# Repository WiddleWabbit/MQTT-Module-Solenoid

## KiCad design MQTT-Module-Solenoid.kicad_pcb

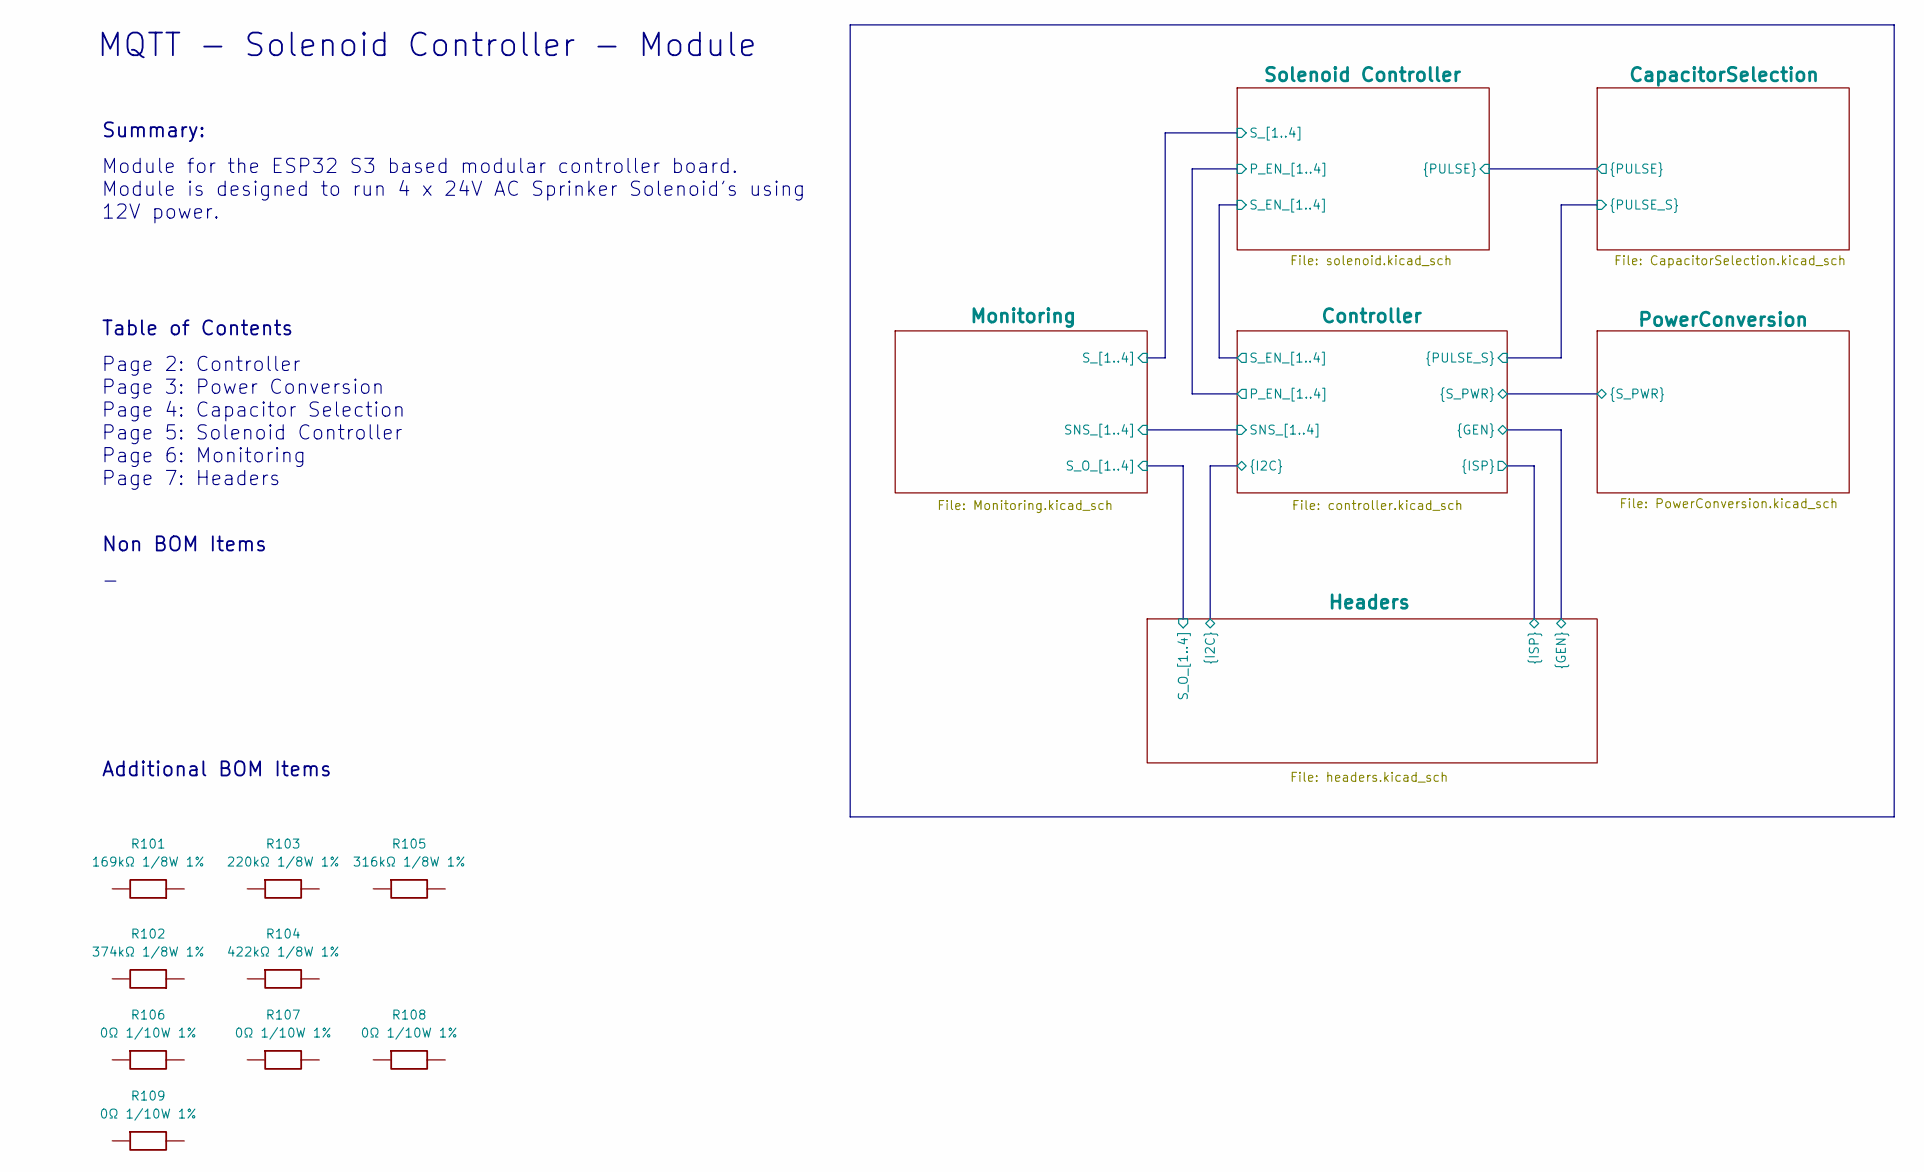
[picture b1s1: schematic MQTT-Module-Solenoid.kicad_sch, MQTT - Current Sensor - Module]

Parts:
R101: 169kΩ 1/8W 1%; RESC2013X65N; Manufacturer Part No 0805W8F1693T5E; JLCPCB Part # C17488
R102: 374kΩ 1/8W 1%; RESC2013X65N; Manufacturer Part No CRCW0805374KFKEA; JLCPCB Part # C2080711
R103: 220kΩ 1/8W 1%; RESC2013X65N; Manufacturer Part No 0805W8F2203T5E; JLCPCB Part # C17556
R104: 422kΩ 1/8W 1%; RESC2013X65N; Manufacturer Part No 0805W8F4223T5E; JLCPCB Part # C17688
R105: 316kΩ 1/8W 1%; RESC2013X65N; Manufacturer Part No 0805W8F3163T5E; JLCPCB Part # C407398
R106, R107, R108, R109: 0Ω 1/10W 1%; RESC1608X55N; Manufacturer Part No 0603WAF0000T5E; JLCPCB Part # C21189

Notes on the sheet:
MQTT - Solenoid Controller - Module
Additional BOM Items
Summary:
Non BOM Items
Page 2: Controller Page 3: Power Conversion Page 4: Capacitor Selection Page 5: Solenoid Controller Page 6: Monitoring Page 7: Headers
Table of Contents
Module for the ESP32 S3 based modular controller board. Module is designed to run 4 x 24V AC Sprinker Solenoid's using 12V power.

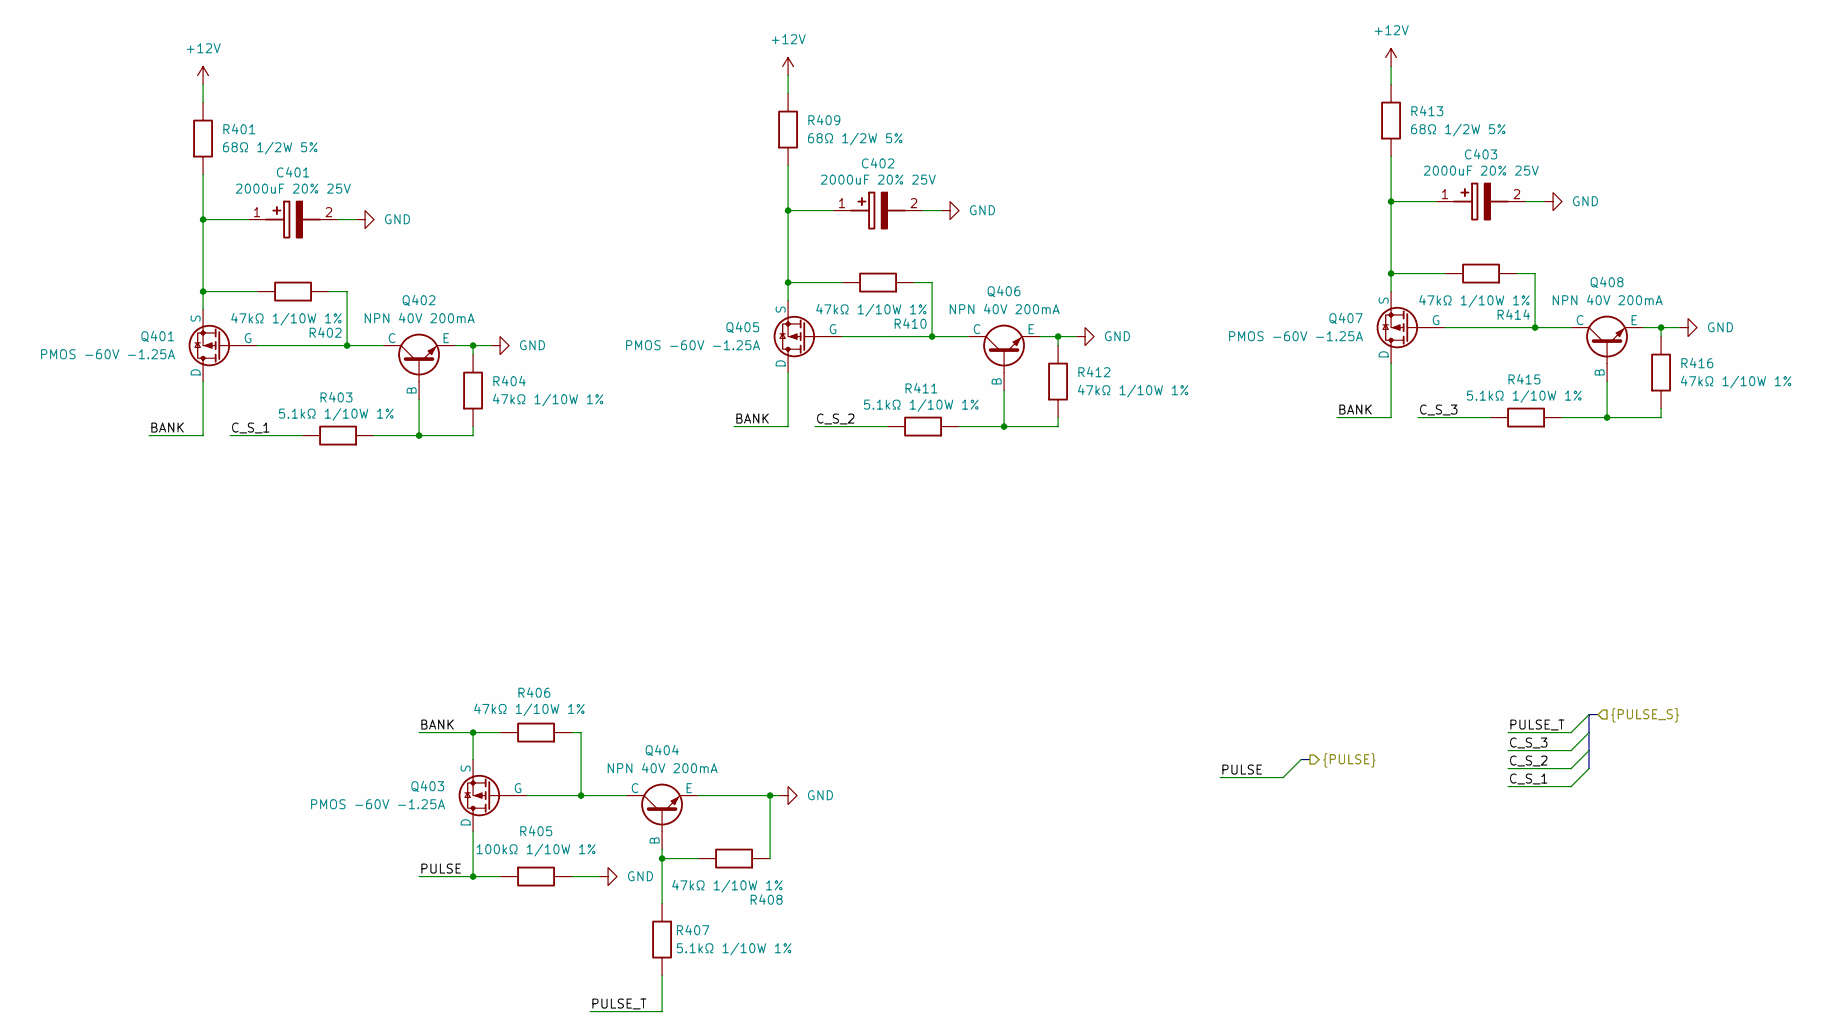
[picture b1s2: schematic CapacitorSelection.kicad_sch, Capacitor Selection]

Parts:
C401, C402, C403: 2000uF 20% 25V; CP_Radial_D12.5mm_P5.00mm; Mouser Part Number 667-EEU-FP1E202
Q401, Q403, Q405, Q407: PMOS -60V -1.25A; SOT-23-3 - FDN5618P; Manufacturer Part No FDN5618P; JLCPCB Part # C400792
Q402, Q404, Q406, Q408: NPN 40V 200mA; SOT-23; Manufacturer Part No MMBT3904LT1G; JLCPCB Part # C81464
R401, R409, R413: 68Ω 1/2W 5%; R_1210_3225Metric; Manufacturer Part No 1210W2J0680T5E; JLCPCB Part # C473019
R402, R404, R406, R408, R410, R412, R414, R416: 47kΩ 1/10W 1%; RESC1608X55N; Manufacturer Part No 0603WAF4702T5E; JLCPCB Part # C25819
R403, R407, R411, R415: 5.1kΩ 1/10W 1%; RESC1608X55N; Mouser Part Number 303-0603WAF5101T5E
R405: 100kΩ 1/10W 1%; RESC1608X55N; Mouser Part Number 303-0805W8F1003T5E

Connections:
+12V: R401.2, R409.2, R413.2; also elsewhere on the board
/CapacitorSelection/BANK: Q401.3 (D), Q403.2 (S), Q405.3 (D), Q407.3 (D), R406.2
/CapacitorSelection/C_S_1: R403.2; also elsewhere on the board
/CapacitorSelection/C_S_2: R411.2; also elsewhere on the board
/CapacitorSelection/C_S_3: R415.2; also elsewhere on the board
/CapacitorSelection/PULSE: Q403.3 (D), R405.1; also elsewhere on the board
/CapacitorSelection/PULSE_T: R407.2; also elsewhere on the board
GND: C401.2 (-), C402.2 (-), C403.2 (-), Q402.2 (E), Q404.2 (E), Q406.2 (E), Q408.2 (E), R404.2, R405.2, R408.1, R412.2, R416.2; also elsewhere on the board
unnamed: C401.1 (+), Q401.2 (S), R401.1, R402.2
unnamed: C402.1 (+), Q405.2 (S), R409.1, R410.2
unnamed: C403.1 (+), Q407.2 (S), R413.1, R414.2
unnamed: Q401.1 (G), Q402.3 (C), R402.1
unnamed: Q402.1 (B), R403.1, R404.1
unnamed: Q403.1 (G), Q404.3 (C), R406.1
unnamed: Q404.1 (B), R407.1, R408.2
unnamed: Q405.1 (G), Q406.3 (C), R410.1
unnamed: Q406.1 (B), R411.1, R412.1
unnamed: Q407.1 (G), Q408.3 (C), R414.1
unnamed: Q408.1 (B), R415.1, R416.1

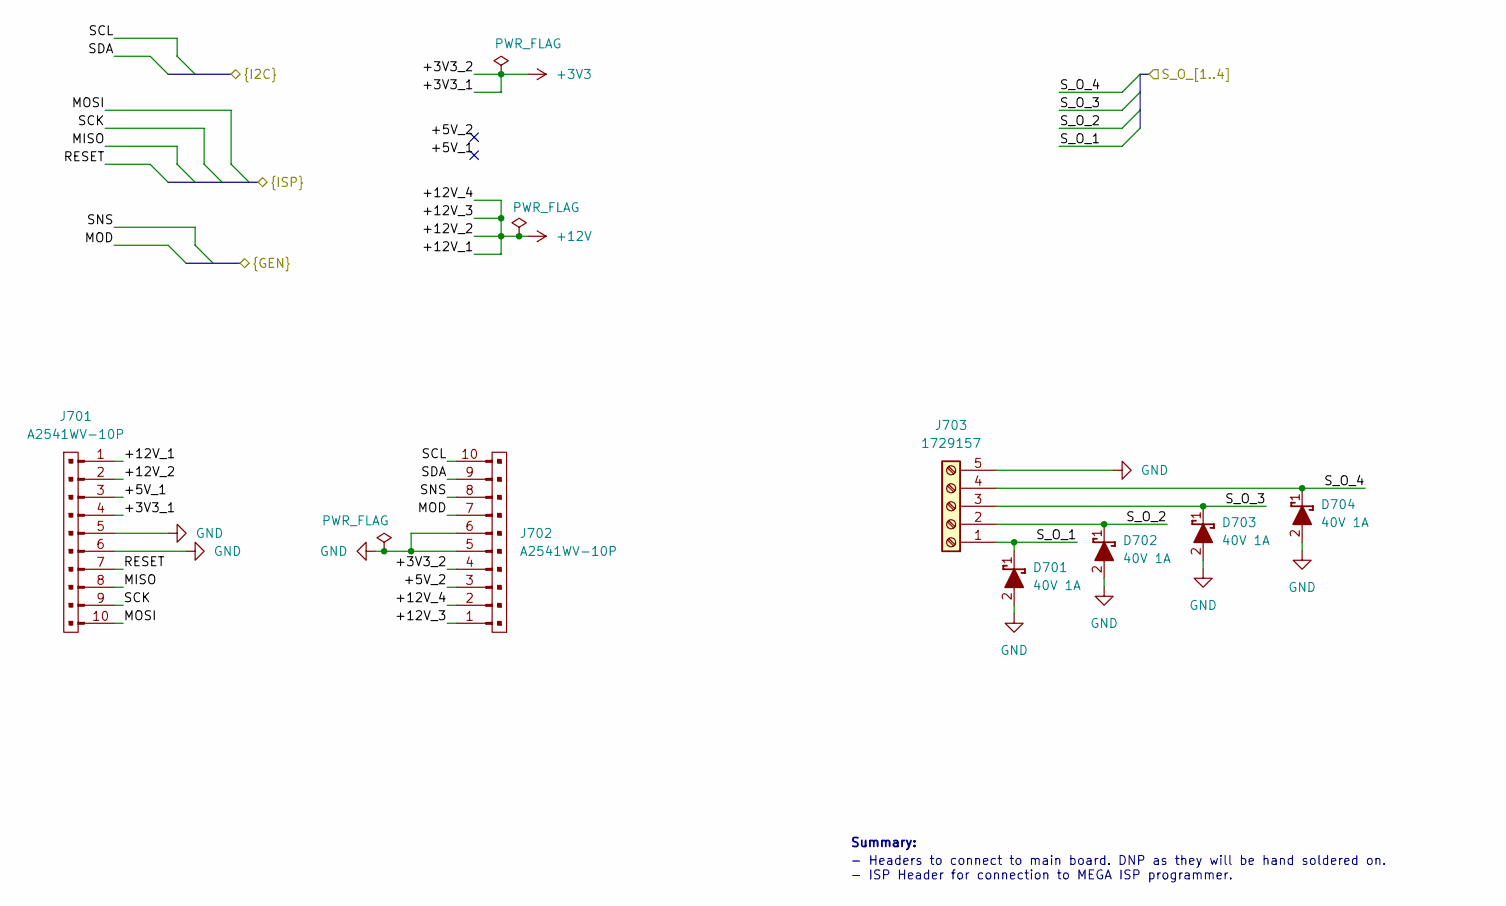
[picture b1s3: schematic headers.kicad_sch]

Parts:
D701, D702, D703, D704: 40V 1A; D_SOD-323F; Manufacturer Part No 1N5819WS; JLCPCB Part # C191023
J701, J702: A2541WV-10P; PinHeader_1x10_P2.54mm_Vertical_Male; Manufacturer Part No A2541WV-10P; JLCPCB Part # C225485
J703: 1729157; Mouser Part Number 651-1729157

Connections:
+3V3: J701.4, J702.4; also elsewhere on the board
+12V: J701.1, J701.2, J702.1, J702.2; also elsewhere on the board
/Controller/MISO: J701.8; also elsewhere on the board
/Controller/MOD: J702.7; also elsewhere on the board
/Controller/MOSI: J701.10; also elsewhere on the board
/Controller/RESET: J701.7; also elsewhere on the board
/Controller/SCK: J701.9; also elsewhere on the board
/Controller/SCL: J702.10; also elsewhere on the board
/Controller/SDA: J702.9; also elsewhere on the board
/Controller/SNS: J702.8; also elsewhere on the board
/Headers/+5V_1: J701.3
/Headers/+5V_2: J702.3
/Headers/S_O_1: D701.1 (K), J703.1; also elsewhere on the board
/Headers/S_O_2: D702.1 (K), J703.2; also elsewhere on the board
/Headers/S_O_3: D703.1 (K), J703.3; also elsewhere on the board
/Headers/S_O_4: D704.1 (K), J703.4; also elsewhere on the board
GND: D701.2 (A), D702.2 (A), D703.2 (A), D704.2 (A), J701.5, J701.6, J702.5, J702.6, J703.5; also elsewhere on the board

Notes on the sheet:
Summary:
- Headers to connect to main board. DNP as they will be hand soldered on. - ISP Header for connection to MEGA ISP programmer.

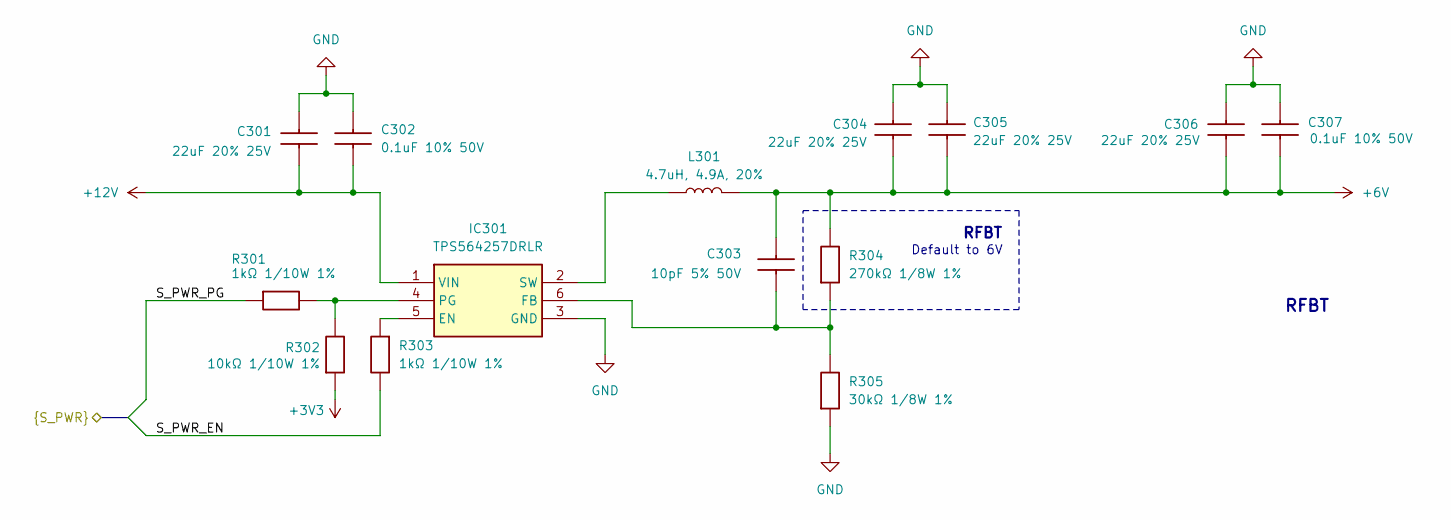
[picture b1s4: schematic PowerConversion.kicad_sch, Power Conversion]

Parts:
C301, C304, C305, C306: 22uF 20% 25V; CAPC2012X75N; Manufacturer Part No CL21A226MAQNNNE; JLCPCB Part # C45783
C302, C307: 0.1uF 10% 50V; CAPC1608X90N; Mouser Part Number 603-CC603KRX7R9BB104
C303: 10pF 5% 50V; CAPC1608X90N; Manufacturer Part No CL10C100JB8NNNC; JLCPCB Part # C1634
IC301: TPS564257DRLR; SOT-563; Mouser Part Number 595-TPS564257DRLR
L301: 4.7uH, 4.9A, 20%; SMD,6x6mm; Manufacturer Part No SMNR6045-4R7MT; JLCPCB Part # C135302
R301, R303: 1kΩ 1/10W 1%; RESC1608X55N; Manufacturer Part No 0603WAF1001T5E; JLCPCB Part # C21190
R302: 10kΩ 1/10W 1%; RESC1608X55N; Mouser Part Number 303-0805W8F1002T5E
R304: 270kΩ 1/8W 1%; RESC2013X65N; Manufacturer Part No 0805W8F2703T5E; JLCPCB Part # C17589
R305: 30kΩ 1/8W 1%; RESC2013X65N; Manufacturer Part No 0805W8F3002T5E; JLCPCB Part # C17621

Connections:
+3V3: R302.1; also elsewhere on the board
+6V: C303.2, C304.1, C305.1, C306.1, C307.1, L301.2, R304.2; also elsewhere on the board
+12V: C301.1, C302.1, IC301.1 (VIN); also elsewhere on the board
/Controller/S_PWR_EN: R303.2; also elsewhere on the board
/Controller/S_PWR_PG: R301.1; also elsewhere on the board
GND: C301.2, C302.2, C304.2, C305.2, C306.2, C307.2, IC301.3 (GND), R305.1; also elsewhere on the board
unnamed: IC301.5 (EN), R303.1
unnamed: C303.1, IC301.6 (FB), R304.1, R305.2
unnamed: IC301.4 (PG), R301.2, R302.2
unnamed: IC301.2 (SW), L301.1

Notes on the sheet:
Default to 6V
RFBT

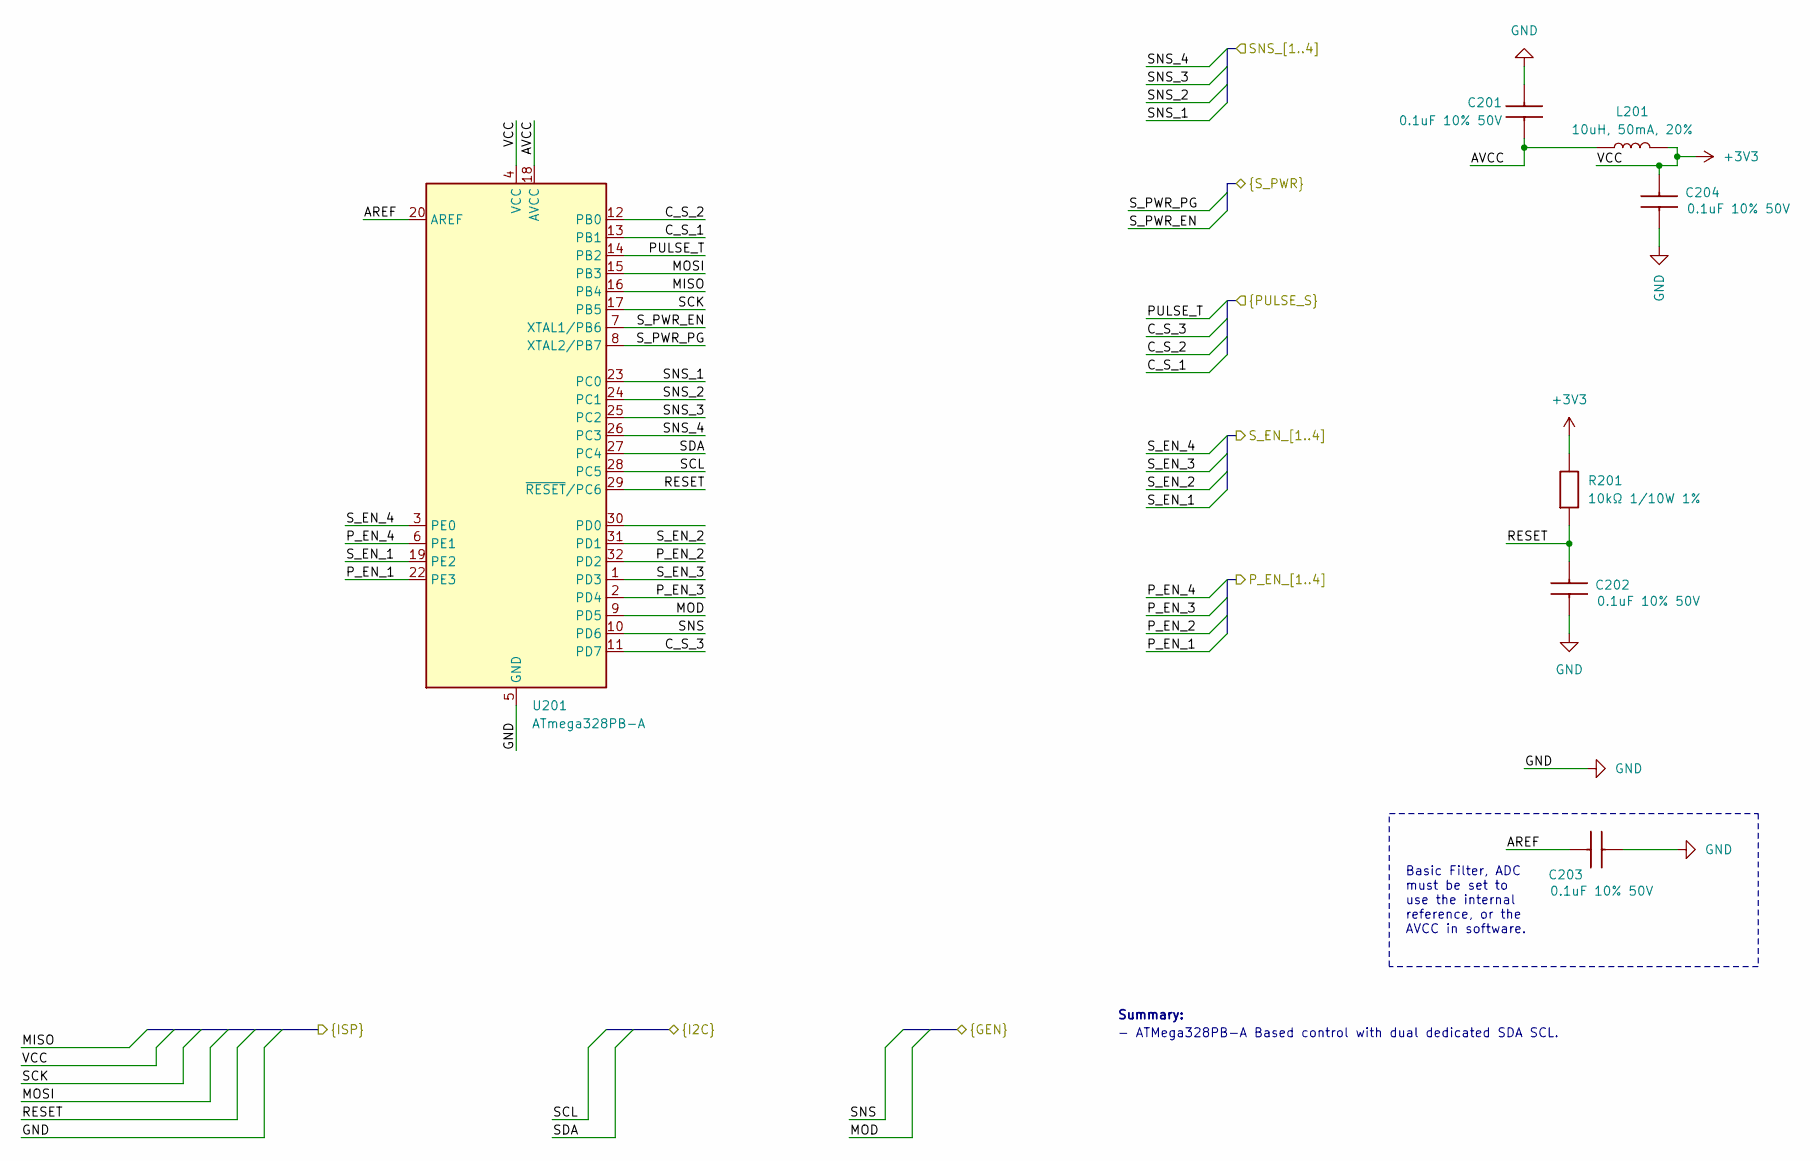
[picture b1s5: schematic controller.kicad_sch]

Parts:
C201, C202, C203, C204: 0.1uF 10% 50V; CAPC1608X90N; Mouser Part Number 603-CC603KRX7R9BB104
L201: 10uH, 50mA, 20%; L_0603_1608Metric; Manufacturer Part No MCL1608S100MT; JLCPCB Part # C51942
R201: 10kΩ 1/10W 1%; RESC1608X55N; Mouser Part Number 303-0805W8F1002T5E
U201: ATmega328PB-A; TQFP-32_7x7mm_P0.8mm; Manufacturer Part No ATMEGA328PB-AU; JLCPCB Part # C132230

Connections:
+3V3: C204.2, L201.2, R201.2, U201.4 (VCC); also elsewhere on the board
/CapacitorSelection/C_S_1: U201.13 (PB1); also elsewhere on the board
/CapacitorSelection/C_S_2: U201.12 (PB0); also elsewhere on the board
/CapacitorSelection/C_S_3: U201.11 (PD7); also elsewhere on the board
/CapacitorSelection/PULSE_T: U201.14 (PB2); also elsewhere on the board
/Controller/AREF: C203.1, U201.20 (AREF)
/Controller/AVCC: C201.1, L201.1, U201.18 (AVCC)
/Controller/MISO: U201.16 (PB4); also elsewhere on the board
/Controller/MOD: U201.9 (PD5); also elsewhere on the board
/Controller/MOSI: U201.15 (PB3); also elsewhere on the board
/Controller/P_EN_1: U201.22 (PE3); also elsewhere on the board
/Controller/P_EN_2: U201.32 (PD2); also elsewhere on the board
/Controller/P_EN_3: U201.2 (PD4); also elsewhere on the board
/Controller/P_EN_4: U201.6 (PE1); also elsewhere on the board
/Controller/RESET: C202.1, R201.1, U201.29 (~RESET/PC6); also elsewhere on the board
/Controller/SCK: U201.17 (PB5); also elsewhere on the board
/Controller/SCL: U201.28 (PC5); also elsewhere on the board
/Controller/SDA: U201.27 (PC4); also elsewhere on the board
/Controller/SNS: U201.10 (PD6); also elsewhere on the board
/Controller/SNS_1: U201.23 (PC0); also elsewhere on the board
/Controller/SNS_2: U201.24 (PC1); also elsewhere on the board
/Controller/SNS_3: U201.25 (PC2); also elsewhere on the board
/Controller/SNS_4: U201.26 (PC3); also elsewhere on the board
/Controller/S_EN_1: U201.19 (PE2); also elsewhere on the board
/Controller/S_EN_2: U201.31 (PD1); also elsewhere on the board
/Controller/S_EN_3: U201.1 (PD3); also elsewhere on the board
/Controller/S_EN_4: U201.3 (PE0); also elsewhere on the board
/Controller/S_PWR_EN: U201.7 (XTAL1/PB6); also elsewhere on the board
/Controller/S_PWR_PG: U201.8 (XTAL2/PB7); also elsewhere on the board
GND: C201.2, C202.2, C203.2, C204.1, U201.5 (GND), U201.21 (GND); also elsewhere on the board

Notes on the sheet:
Basic Filter, ADC must be set to use the internal reference, or the AVCC in software.
- ATMega328PB-A Based control with dual dedicated SDA SCL.
Summary:

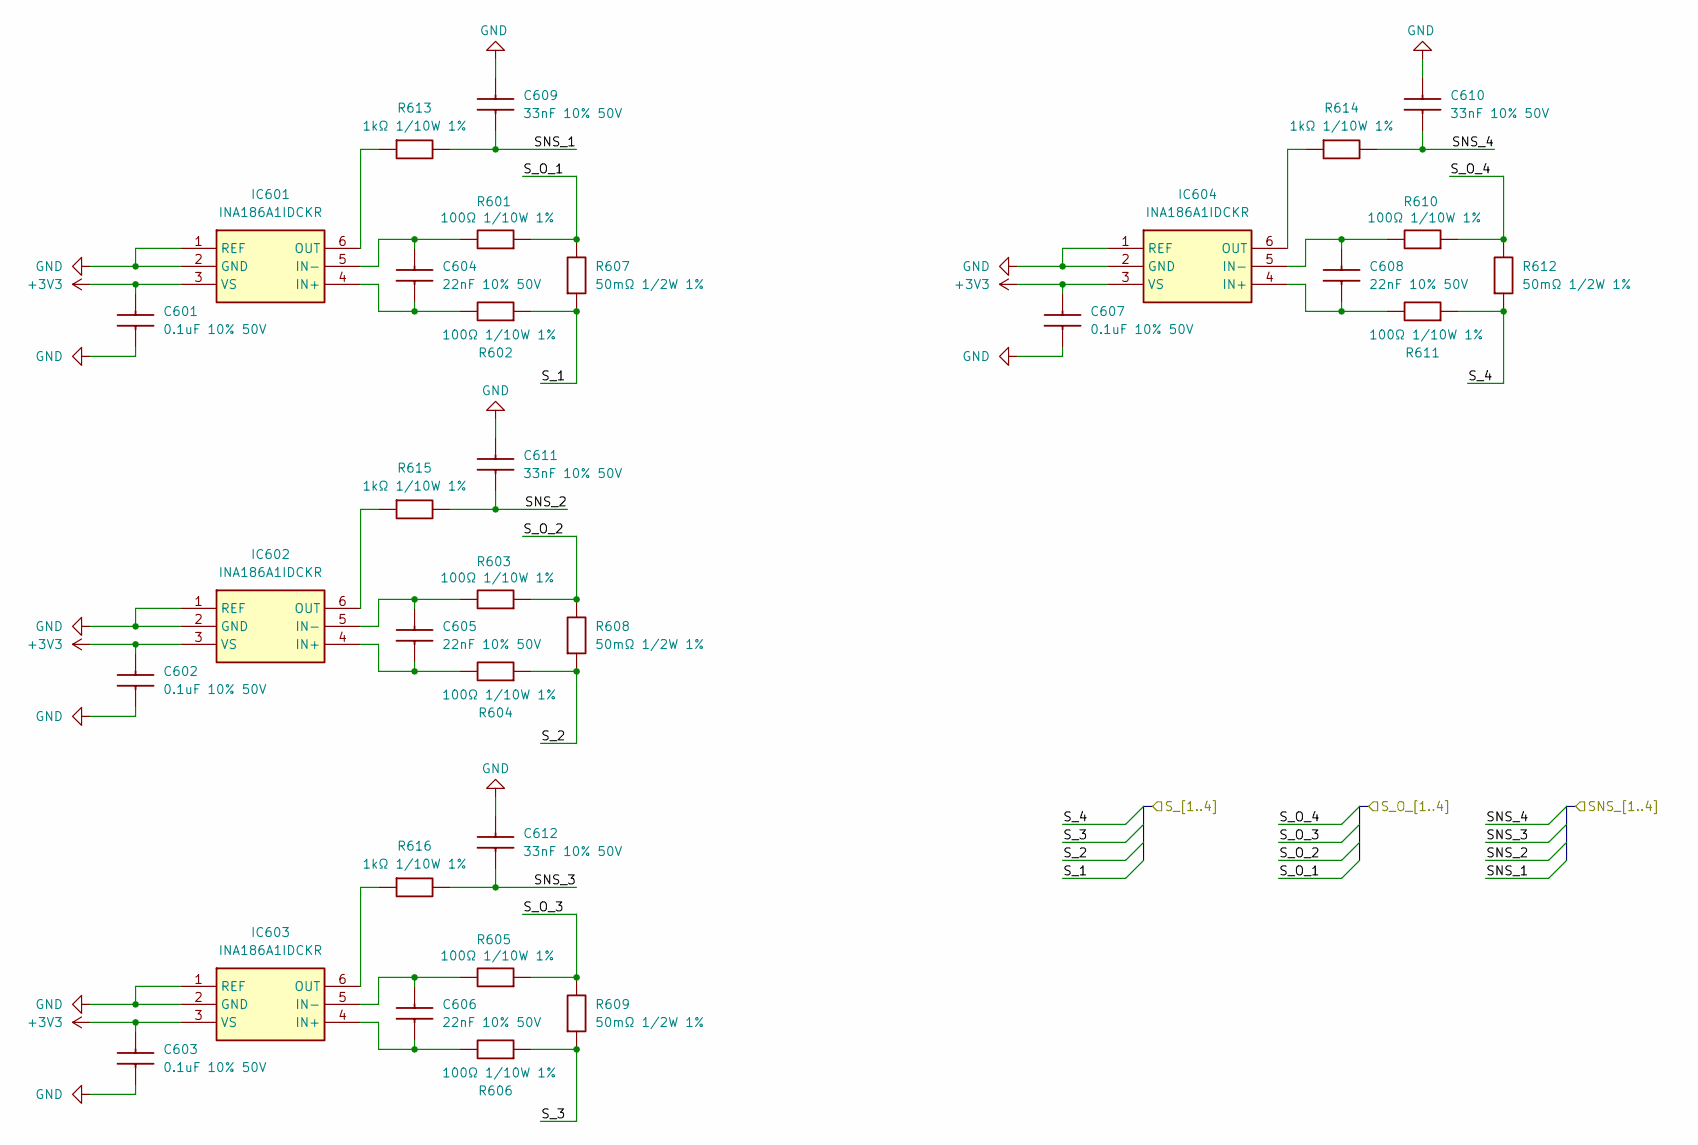
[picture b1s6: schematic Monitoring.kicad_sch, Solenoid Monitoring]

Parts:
C601, C602, C603, C607: 0.1uF 10% 50V; CAPC1608X90N; Mouser Part Number 603-CC603KRX7R9BB104
C604, C605, C606, C608: 22nF 10% 50V; CAPC1608X90N; Manufacturer Part No CL10B223KB8NNNC; JLCPCB Part # C21122
C609, C610, C611, C612: 33nF 10% 50V; CAPC1608X90N; Manufacturer Part No CL10B333KB8NNNC; JLCPCB Part # C21117
IC601, IC602, IC603, IC604: INA186A1IDCKR; SOT65P210X110-6N; Mouser Part Number 595-INA186A1IDCKR
R601, R602, R603, R604, R605, R606, R610, R611: 100Ω 1/10W 1%; RESC1608X55N; Manufacturer Part No 0603WAF1000T5E; JLCPCB Part # C22775
R607, R608, R609, R612: 50mΩ 1/2W 1%; RESC2012X60N; Manufacturer Part No PE0805FRF470R05L; JLCPCB Part # C858604
R613, R614, R615, R616: 1kΩ 1/10W 1%; RESC1608X55N; Manufacturer Part No 0603WAF1001T5E; JLCPCB Part # C21190

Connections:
+3V3: C601.2, C602.2, C603.2, C607.2, IC601.3 (VS), IC602.3 (VS), IC603.3 (VS), IC604.3 (VS); also elsewhere on the board
/Controller/SNS_1: C609.1, R613.2; also elsewhere on the board
/Controller/SNS_2: C611.1, R615.2; also elsewhere on the board
/Controller/SNS_3: C612.1, R616.2; also elsewhere on the board
/Controller/SNS_4: C610.1, R614.2; also elsewhere on the board
/Headers/S_O_1: R601.1, R607.2; also elsewhere on the board
/Headers/S_O_2: R603.1, R608.2; also elsewhere on the board
/Headers/S_O_3: R605.1, R609.2; also elsewhere on the board
/Headers/S_O_4: R610.1, R612.2; also elsewhere on the board
/Monitoring/S_1: R602.1, R607.1; also elsewhere on the board
/Monitoring/S_2: R604.1, R608.1; also elsewhere on the board
/Monitoring/S_3: R606.1, R609.1; also elsewhere on the board
/Monitoring/S_4: R611.1, R612.1; also elsewhere on the board
GND: C601.1, C602.1, C603.1, C607.1, C609.2, C610.2, C611.2, C612.2, IC601.1 (REF), IC601.2 (GND), IC602.1 (REF), IC602.2 (GND), IC603.1 (REF), IC603.2 (GND), IC604.1 (REF), IC604.2 (GND); also elsewhere on the board
unnamed: C604.1, IC601.4 (IN+), R602.2
unnamed: C604.2, IC601.5 (IN-), R601.2
unnamed: IC601.6 (OUT), R613.1
unnamed: C605.1, IC602.4 (IN+), R604.2
unnamed: C605.2, IC602.5 (IN-), R603.2
unnamed: IC602.6 (OUT), R615.1
unnamed: C606.1, IC603.4 (IN+), R606.2
unnamed: C606.2, IC603.5 (IN-), R605.2
unnamed: IC603.6 (OUT), R616.1
unnamed: C608.1, IC604.4 (IN+), R611.2
unnamed: C608.2, IC604.5 (IN-), R610.2
unnamed: IC604.6 (OUT), R614.1

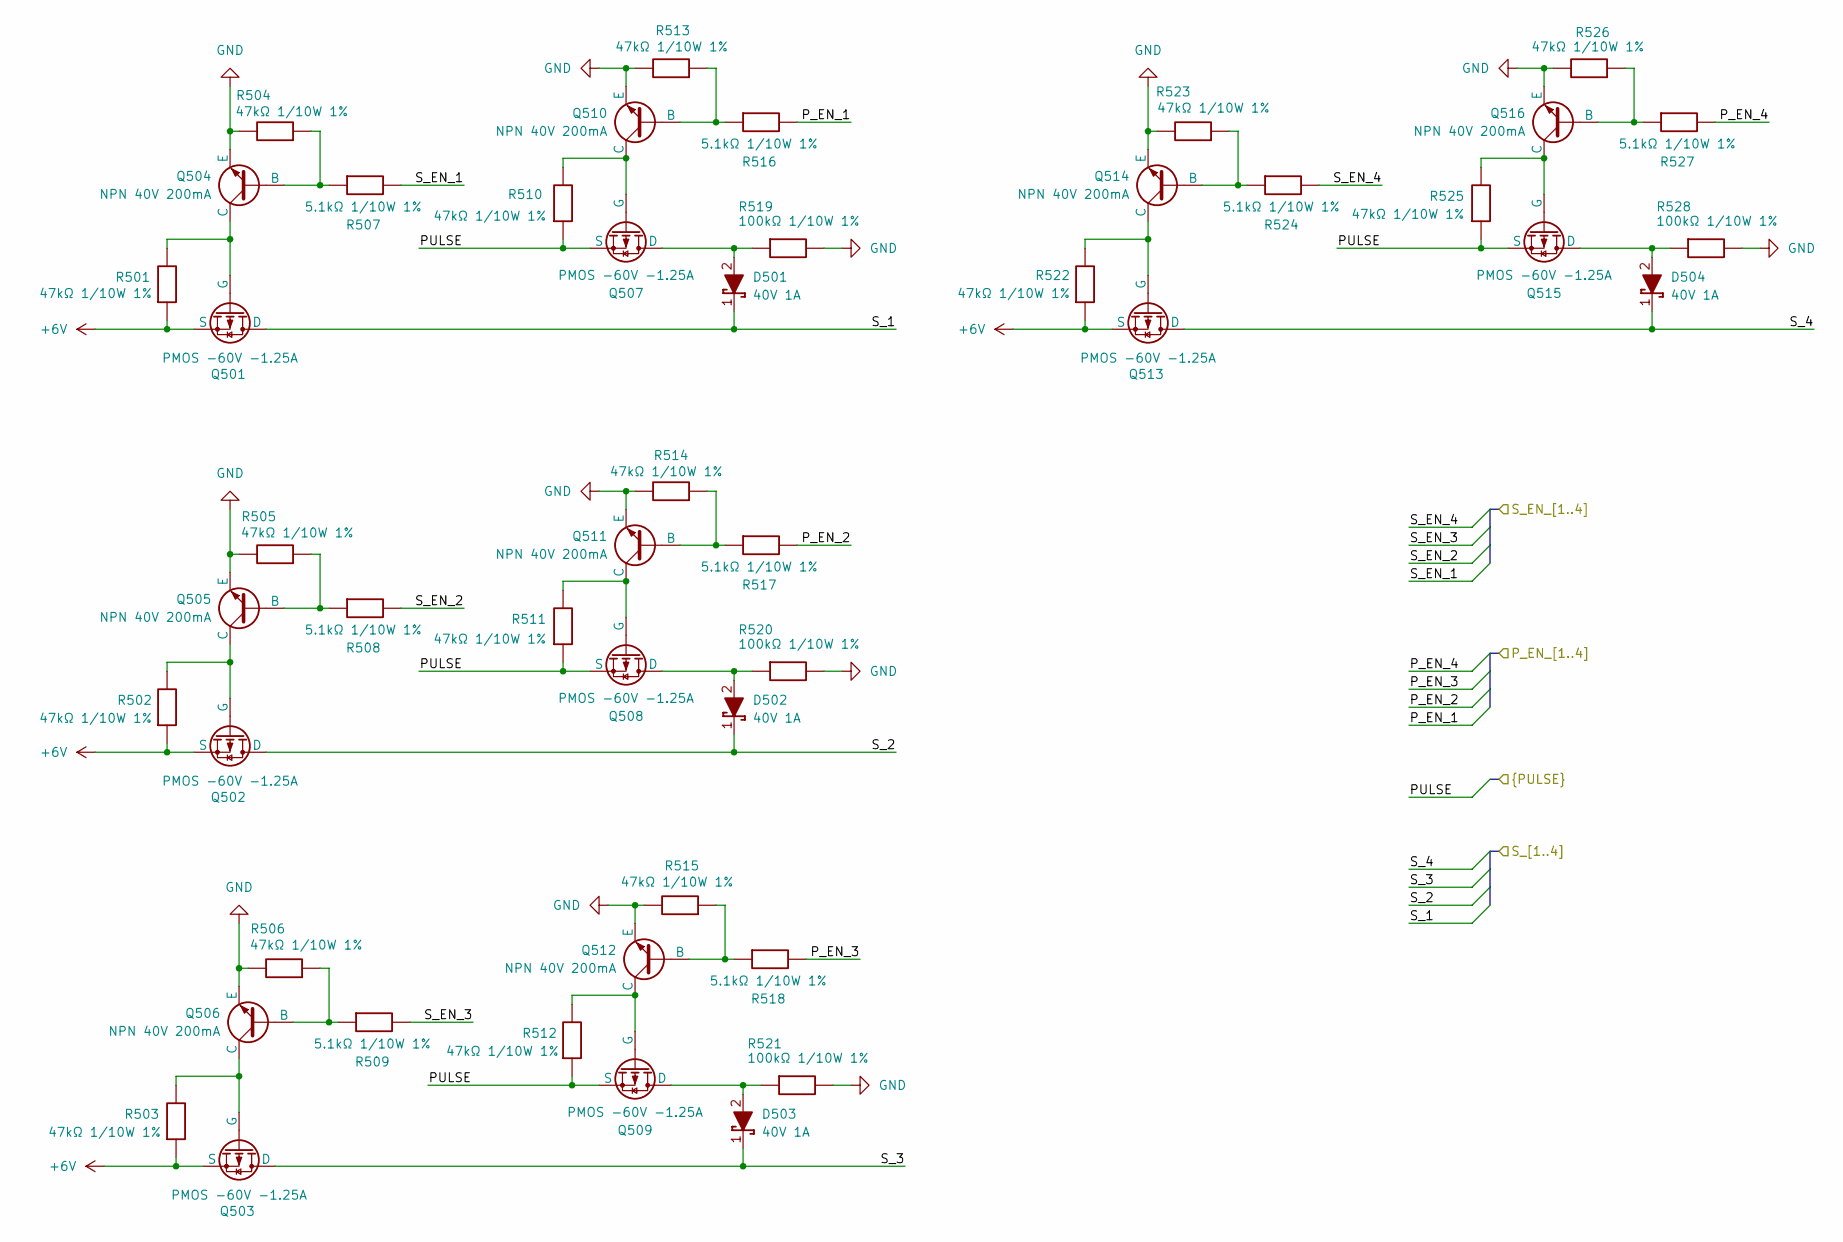
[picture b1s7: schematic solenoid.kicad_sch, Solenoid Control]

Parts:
D501, D502, D503, D504: 40V 1A; D_SOD-323F; Manufacturer Part No 1N5819WS; JLCPCB Part # C191023
Q501, Q502, Q503, Q507, Q508, Q509, Q513, Q515: PMOS -60V -1.25A; SOT-23-3 - FDN5618P; Manufacturer Part No FDN5618P; JLCPCB Part # C400792
Q504, Q505, Q506, Q510, Q511, Q512, Q514, Q516: NPN 40V 200mA; SOT-23; Manufacturer Part No MMBT3904LT1G; JLCPCB Part # C81464
R501, R502, R503, R504, R505, R506, R510, R511, R512, R513, R514, R515, R522, R523, R525, R526: 47kΩ 1/10W 1%; RESC1608X55N; Manufacturer Part No 0603WAF4702T5E; JLCPCB Part # C25819
R507, R508, R509, R516, R517, R518, R524, R527: 5.1kΩ 1/10W 1%; RESC1608X55N; Mouser Part Number 303-0603WAF5101T5E
R519, R520, R521, R528: 100kΩ 1/10W 1%; RESC1608X55N; Mouser Part Number 303-0805W8F1003T5E

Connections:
+6V: Q501.2 (S), Q502.2 (S), Q503.2 (S), Q513.2 (S), R501.1, R502.1, R503.1, R522.1; also elsewhere on the board
/CapacitorSelection/PULSE: Q507.2 (S), Q508.2 (S), Q509.2 (S), Q515.2 (S), R510.1, R511.1, R512.1, R525.1; also elsewhere on the board
/Controller/P_EN_1: R516.2; also elsewhere on the board
/Controller/P_EN_2: R517.2; also elsewhere on the board
/Controller/P_EN_3: R518.2; also elsewhere on the board
/Controller/P_EN_4: R527.2; also elsewhere on the board
/Controller/S_EN_1: R507.2; also elsewhere on the board
/Controller/S_EN_2: R508.2; also elsewhere on the board
/Controller/S_EN_3: R509.2; also elsewhere on the board
/Controller/S_EN_4: R524.2; also elsewhere on the board
/Monitoring/S_1: D501.1 (K), Q501.3 (D); also elsewhere on the board
/Monitoring/S_2: D502.1 (K), Q502.3 (D); also elsewhere on the board
/Monitoring/S_3: D503.1 (K), Q503.3 (D); also elsewhere on the board
/Monitoring/S_4: D504.1 (K), Q513.3 (D); also elsewhere on the board
GND: Q504.2 (E), Q505.2 (E), Q506.2 (E), Q510.2 (E), Q511.2 (E), Q512.2 (E), Q514.2 (E), Q516.2 (E), R504.2, R505.2, R506.2, R513.2, R514.2, R515.2, R519.2, R520.2, R521.2, R523.2, R526.2, R528.2; also elsewhere on the board
unnamed: D501.2 (A), Q507.3 (D), R519.1
unnamed: D502.2 (A), Q508.3 (D), R520.1
unnamed: D503.2 (A), Q509.3 (D), R521.1
unnamed: D504.2 (A), Q515.3 (D), R528.1
unnamed: Q501.1 (G), Q504.3 (C), R501.2
unnamed: Q502.1 (G), Q505.3 (C), R502.2
unnamed: Q503.1 (G), Q506.3 (C), R503.2
unnamed: Q504.1 (B), R504.1, R507.1
unnamed: Q505.1 (B), R505.1, R508.1
unnamed: Q506.1 (B), R506.1, R509.1
unnamed: Q507.1 (G), Q510.3 (C), R510.2
unnamed: Q508.1 (G), Q511.3 (C), R511.2
unnamed: Q509.1 (G), Q512.3 (C), R512.2
unnamed: Q510.1 (B), R513.1, R516.1
unnamed: Q511.1 (B), R514.1, R517.1
unnamed: Q512.1 (B), R515.1, R518.1
unnamed: Q513.1 (G), Q514.3 (C), R522.2
unnamed: Q514.1 (B), R523.1, R524.1
unnamed: Q515.1 (G), Q516.3 (C), R525.2
unnamed: Q516.1 (B), R526.1, R527.1

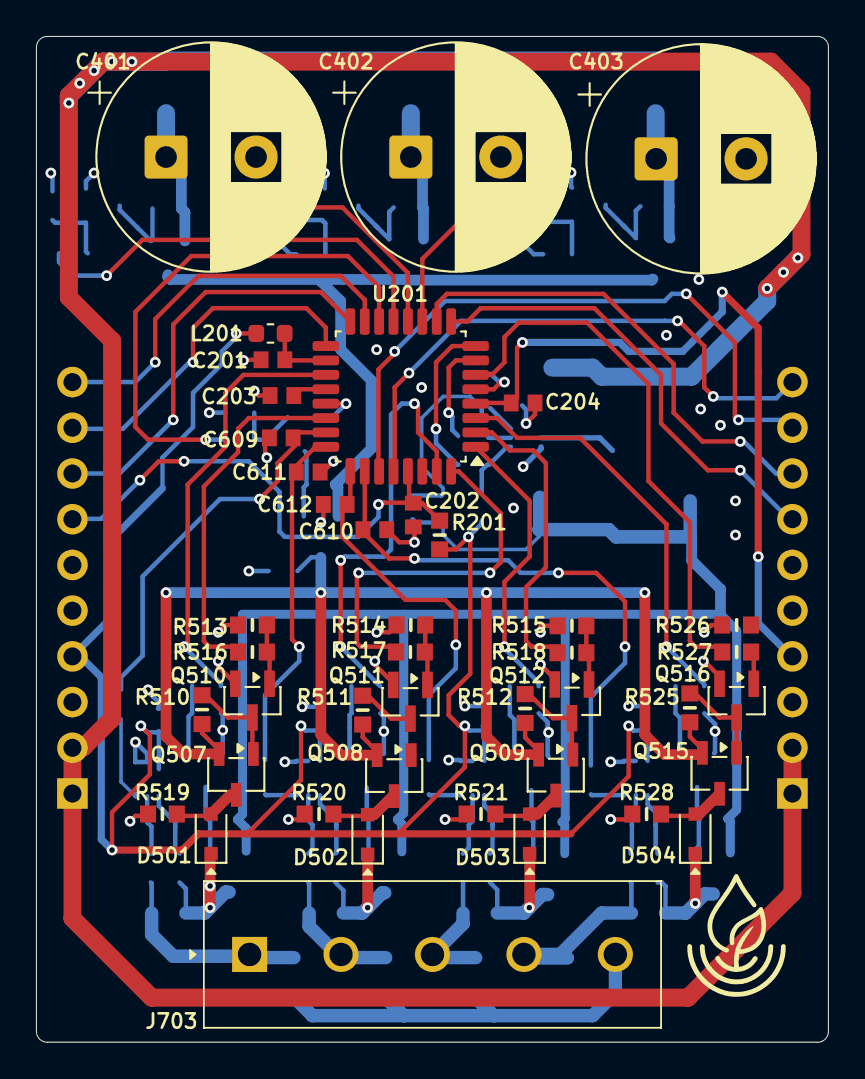
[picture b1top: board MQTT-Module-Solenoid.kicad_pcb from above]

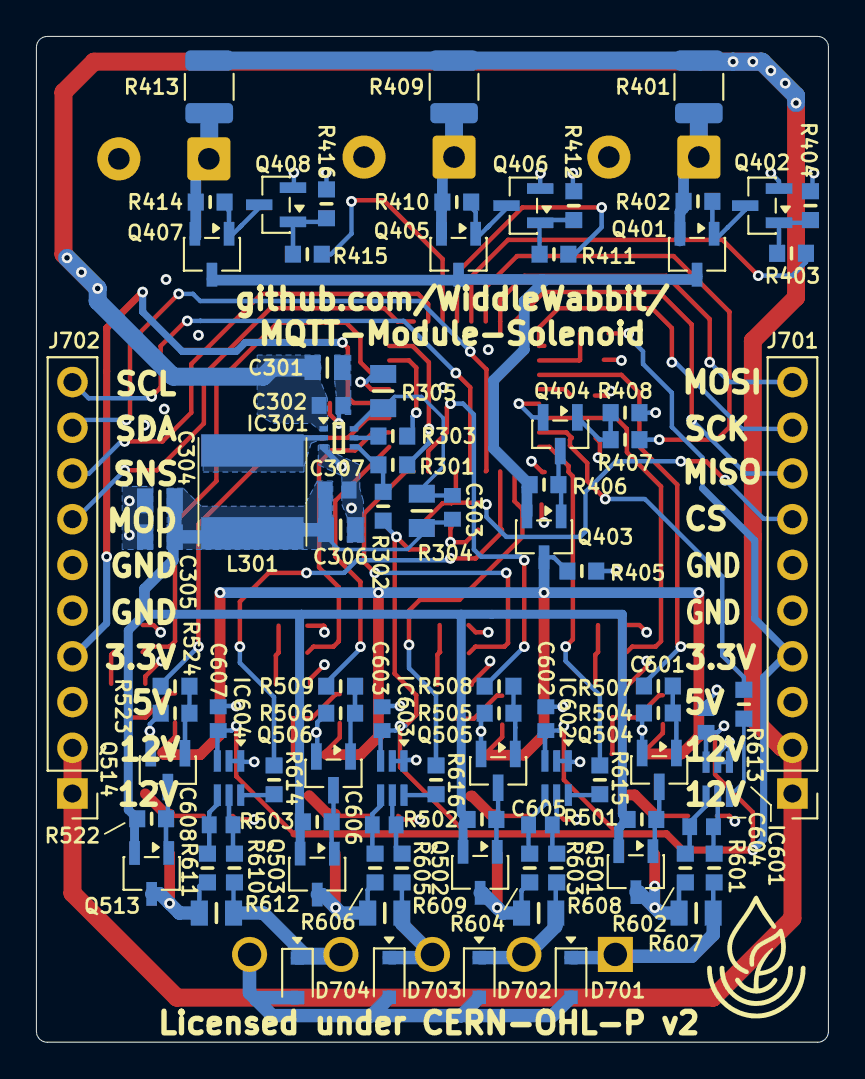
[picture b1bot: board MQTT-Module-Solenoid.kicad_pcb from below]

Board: 4 copper layers, 44.0 x 55.9 mm, 135 parts (92 on the bottom side), 89 nets.

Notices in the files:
MQTT-Module-Solenoid.kicad_pcb:
Licensed under CERN-OHL-P v2
